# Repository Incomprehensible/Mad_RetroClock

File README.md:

# Retro style desk clock

Powered via 5V USB-C interface. Provides a 2S Li-Ion battery pack for autonomous operation.\
Made with 4 IN-12A Nixie Tubes denoting hours & minutes, and smaller INS-1 tubes as the dots.\
Enabled with Wi-Fi connectivity for automatic time synchronization using the Network Time Protocol (NTP).\
Functions as a simple clock and an alarm clock. User interface for the alarm setting is implemented with 2 Set/Unset buttons and rotary encoder.\
There's an MP3-player onboard any melody can be programmed and set as an alarm call.

## Gallery

<details><summary>More photos</summary>

</details>

## Further steps
* Enclosure design
* Add remote app control / IOT host node connectivity
* Better power design to get rid of inrush current issue preventing the device to start up sometimes without USB power attached

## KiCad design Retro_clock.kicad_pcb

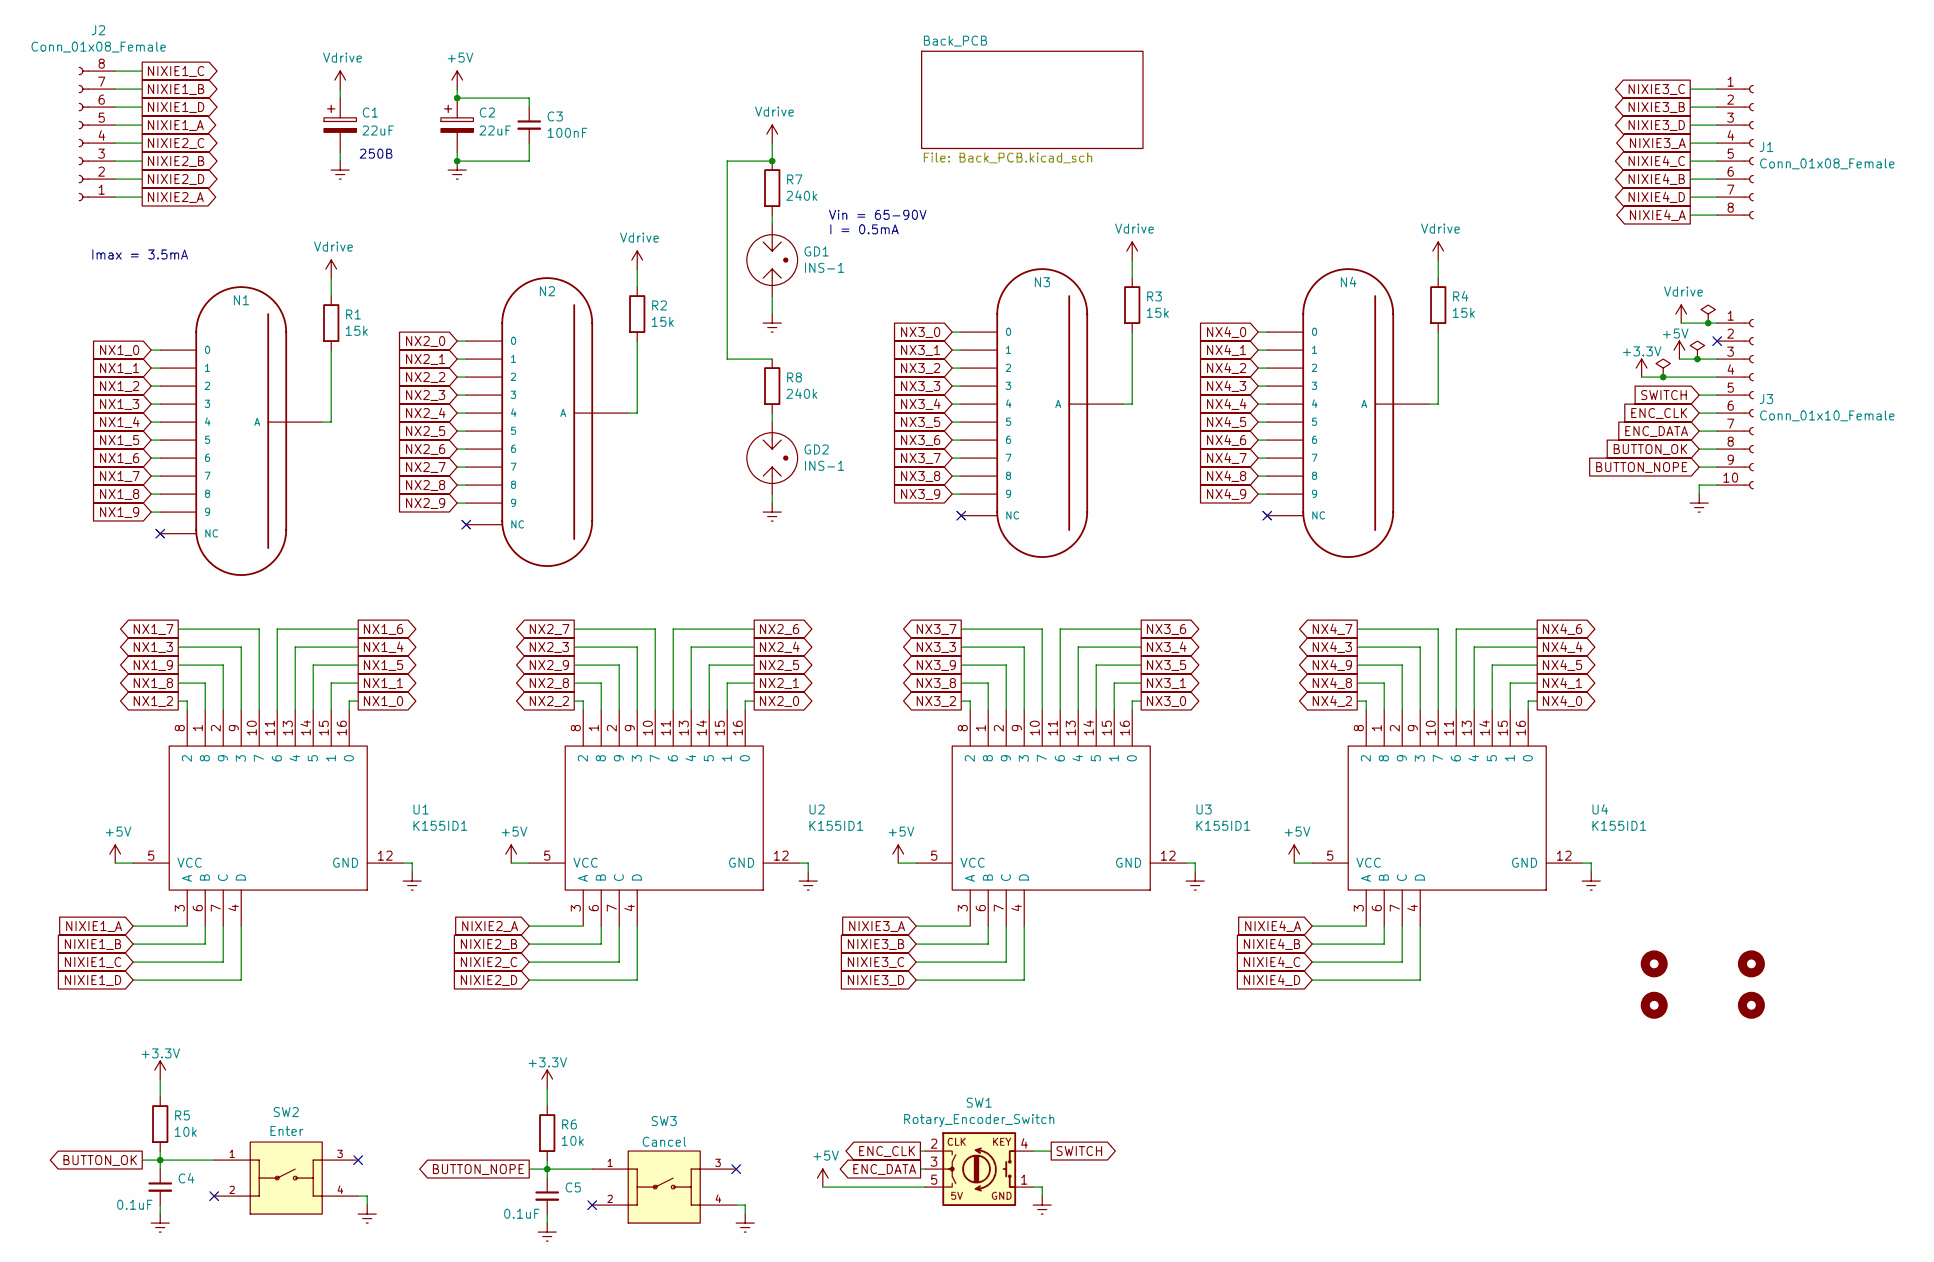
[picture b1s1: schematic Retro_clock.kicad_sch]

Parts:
C1: 22uF; CP_Radial_D10.0mm_P5.00mm
C2: 22uF; CP_EIA-3216-10_Kemet-I_Pad1.58x1.35mm_HandSolder
C3: 100nF; C_0603_1608Metric_Pad1.08x0.95mm_HandSolder
C4, C5: 0.1uF; C_0603_1608Metric_Pad1.08x0.95mm_HandSolder
GD1, GD2: INS-1
H1, H2, H3, H4: MountingHole; MountingHole_2.5mm_Pad_Via
J1, J2: Conn_01x08_Female; PinSocket_1x08_P2.54mm_Vertical
J3: Conn_01x10_Female; PinSocket_1x10_P2.54mm_Vertical
N1, N2, N3, N4: IN-12A
R1, R2, R3, R4: 15k; R_1206_3216Metric_Pad1.30x1.75mm_HandSolder
R5, R6: 10k; R_1206_3216Metric_Pad1.30x1.75mm_HandSolder
R7, R8: 240k; R_0805_2012Metric_Pad1.20x1.40mm_HandSolder
SW1: Rotary_Encoder_Switch; Encoder
SW2: Enter; KLS7-TS6601-13.0-180
SW3: Cancel; KLS7-TS6601-13.0-180
U1, U2, U3, U4: K155ID1; DIP-16_W7.62mm

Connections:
+3.3V: J3.4, R5.1, R6.1
+5V: C2.1, C3.1, J3.3, SW1.5 (5V), U1.5 (VCC), U2.5 (VCC), U3.5 (VCC), U4.5 (VCC)
BUTTON_NOPE: C5.1, J3.9, R6.2, SW3.1
BUTTON_OK: C4.1, J3.8, R5.2, SW2.1
ENC_CLK: J3.6, SW1.2 (CLK)
ENC_DATA: J3.7, SW1.3 (DATA)
Earth: C1.2, C2.2, C3.2, C4.2, C5.2, GD1.2, GD2.2, J3.10, SW1.1 (GND), SW2.4, SW3.4, U1.12 (GND), U2.12 (GND), U3.12 (GND), U4.12 (GND)
NIXIE1_A: J2.5, U1.3 (A)
NIXIE1_B: J2.7, U1.6 (B)
NIXIE1_C: J2.8, U1.7 (C)
NIXIE1_D: J2.6, U1.4 (D)
NIXIE2_A: J2.1, U2.3 (A)
NIXIE2_B: J2.3, U2.6 (B)
NIXIE2_C: J2.4, U2.7 (C)
NIXIE2_D: J2.2, U2.4 (D)
NIXIE3_A: J1.4, U3.3 (A)
NIXIE3_B: J1.2, U3.6 (B)
NIXIE3_C: J1.1, U3.7 (C)
NIXIE3_D: J1.3, U3.4 (D)
NIXIE4_A: J1.8, U4.3 (A)
NIXIE4_B: J1.6, U4.6 (B)
NIXIE4_C: J1.5, U4.7 (C)
NIXIE4_D: J1.7, U4.4 (D)
NX1_0: N1.2 (0), U1.16 (0)
NX1_1: N1.11 (1), U1.15 (1)
NX1_2: N1.10 (2), U1.8 (2)
NX1_3: N1.9 (3), U1.9 (3)
NX1_4: N1.8 (4), U1.13 (4)
NX1_5: N1.7 (5), U1.14 (5)
NX1_6: N1.6, U1.11 (6)
NX1_7: N1.5 (7), U1.10 (7)
NX1_8: N1.4 (8), U1.1 (8)
NX1_9: N1.3 (9), U1.2 (9)
NX2_0: N2.2 (0), U2.16 (0)
NX2_1: N2.11 (1), U2.15 (1)
NX2_2: N2.10 (2), U2.8 (2)
NX2_3: N2.9 (3), U2.9 (3)
NX2_4: N2.8 (4), U2.13 (4)
NX2_5: N2.7 (5), U2.14 (5)
NX2_6: N2.6, U2.11 (6)
NX2_7: N2.5 (7), U2.10 (7)
NX2_8: N2.4 (8), U2.1 (8)
NX2_9: N2.3 (9), U2.2 (9)
NX3_0: N3.2 (0), U3.16 (0)
NX3_1: N3.11 (1), U3.15 (1)
NX3_2: N3.10 (2), U3.8 (2)
NX3_3: N3.9 (3), U3.9 (3)
NX3_4: N3.8 (4), U3.13 (4)
NX3_5: N3.7 (5), U3.14 (5)
NX3_6: N3.6, U3.11 (6)
NX3_7: N3.5 (7), U3.10 (7)
NX3_8: N3.4 (8), U3.1 (8)
NX3_9: N3.3 (9), U3.2 (9)
NX4_0: N4.2 (0), U4.16 (0)
NX4_1: N4.11 (1), U4.15 (1)
NX4_2: N4.10 (2), U4.8 (2)
NX4_3: N4.9 (3), U4.9 (3)
NX4_4: N4.8 (4), U4.13 (4)
NX4_5: N4.7 (5), U4.14 (5)
NX4_6: N4.6, U4.11 (6)
NX4_7: N4.5 (7), U4.10 (7)
NX4_8: N4.4 (8), U4.1 (8)
NX4_9: N4.3 (9), U4.2 (9)
unnamed: GD1.1, R7.2
unnamed: GD2.1, R8.2
unnamed: N1.1 (A), R1.2
unnamed: N2.1 (A), R2.2
unnamed: N3.1 (A), R3.2
unnamed: N4.1 (A), R4.2
SWITCH: J3.5, SW1.4 (KEY)
Vdrive: C1.1, J3.1, R1.1, R2.1, R3.1, R4.1, R7.1, R8.1

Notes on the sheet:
Imax = 3.5mA
Vin = 65-90V I = 0.5mA
250В

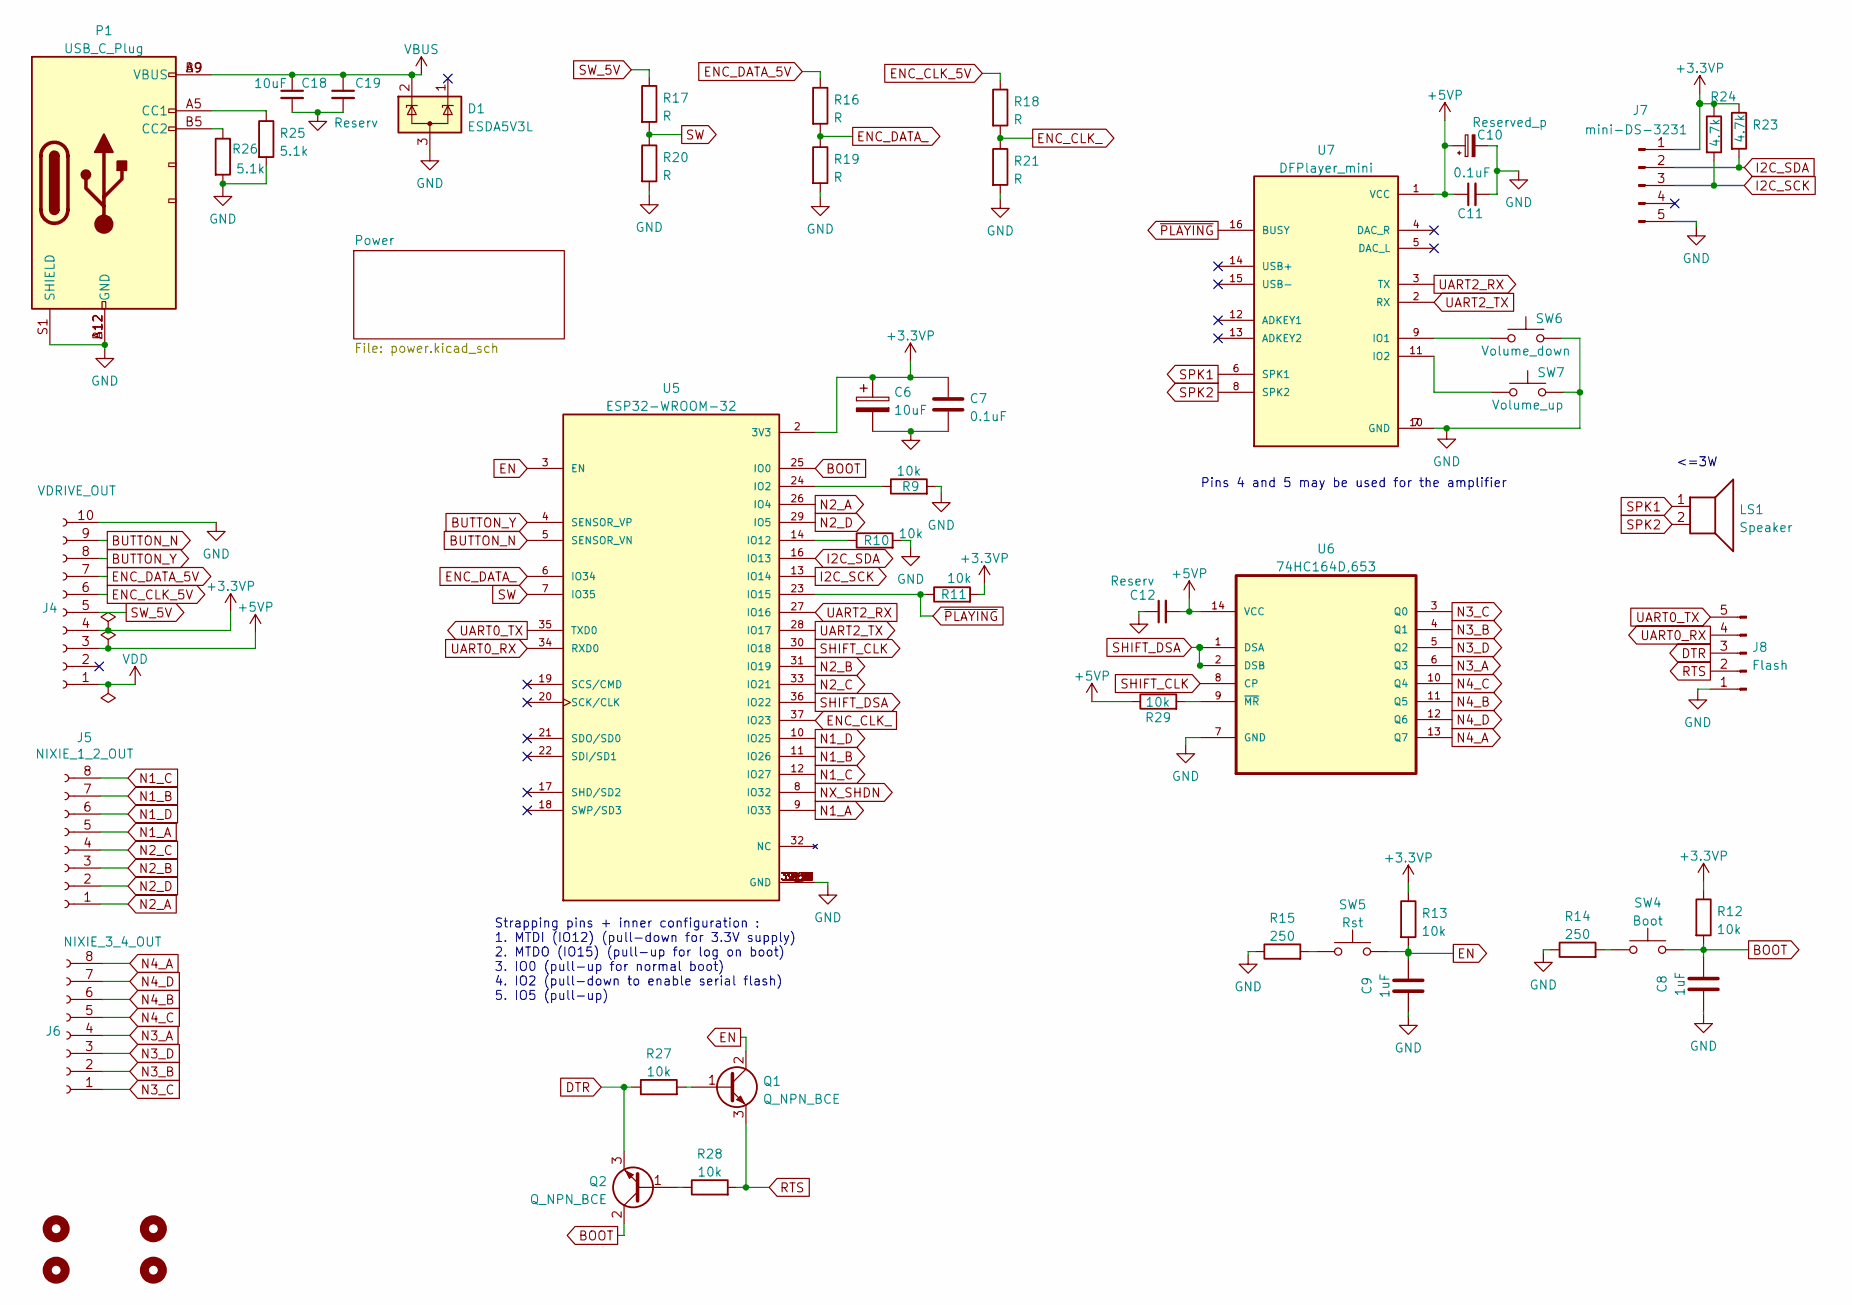
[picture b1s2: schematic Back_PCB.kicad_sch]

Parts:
C6, C18: 10uF; C_0603_1608Metric_Pad1.08x0.95mm_HandSolder
C7, C11: 0.1uF; C_0603_1608Metric_Pad1.08x0.95mm_HandSolder
C8, C9: 1uF; C_0603_1608Metric_Pad1.08x0.95mm_HandSolder
C10: Reserved_p; C_0603_1608Metric_Pad1.08x0.95mm_HandSolder
C12, C19: Reserv; C_0603_1608Metric_Pad1.08x0.95mm_HandSolder
D1: ESDA5V3L; SOT-23
H5, H6, H7, H8: MountingHole; MountingHole_2.5mm_Pad_Via
J4: VDRIVE_OUT; PinSocket_1x10_P2.54mm_Vertical
J5: NIXIE_1_2_OUT; PinSocket_1x08_P2.54mm_Vertical
J6: NIXIE_3_4_OUT; PinSocket_1x08_P2.54mm_Vertical
J7: mini-DS-3231; DS3231-Mini
J8: Flash; PinHeader_1x05_P2.54mm_Vertical
LS1: Speaker; Speaker_conn
P1: USB_C_Plug; usb_c_receptable_hro_type-c-31-m-17
Q1, Q2: Q_NPN_BCE; SOT-23_Handsoldering
R9, R10, R11, R12, R13, R27, R28, R29: 10k; R_0603_1608Metric_Pad0.98x0.95mm_HandSolder
R14, R15: 250; R_0603_1608Metric_Pad0.98x0.95mm_HandSolder
R16, R17, R18, R19, R20, R21: R; R_0603_1608Metric_Pad0.98x0.95mm_HandSolder
R23, R24: 4.7k; R_0603_1608Metric_Pad0.98x0.95mm_HandSolder
R25, R26: 5.1k; R_0603_1608Metric_Pad0.98x0.95mm_HandSolder
SW4: Boot; SW_TS-1187A-B-A-B
SW5: Rst; SW_TS-1187A-B-A-B
SW6: Volume_down; KLS7-TS6601-13.0-180
SW7: Volume_up; KLS7-TS6601-13.0-180
U5: ESP32-WROOM-32; MODULE_ESP32-WROOM-32; PARTREV 2.9
U6: 74HC164D,653; SOIC127P600X175-14N; MPN 74HC164D,653
U7: DFPlayer_mini; MODULE_DFR0299

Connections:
+3.3VP: C6.1, C7.1, J4.4, J7.1, R11.2, R12.1, R13.1, R23.1, R24.1, U5.2 (3V3); also elsewhere on the board
+5VP: C10.1, C11.1, C12.2, J4.3, R29.1, U6.14 (VCC), U7.1 (VCC); also elsewhere on the board
BOOT: C8.2, Q2.2 (C), R12.2, SW4.2, U5.25 (IO0)
BUTTON_N: J4.9, U5.5 (SENSOR_VN)
BUTTON_Y: J4.8, U5.4 (SENSOR_VP)
DTR: J8.3, Q2.3 (E), R27.1
EN: C9.2, Q1.2 (C), R13.2, SW5.2, U5.3 (EN)
ENC_CLK_: R18.2, R21.1, U5.37 (IO23)
ENC_CLK_5V: J4.6, R18.1
ENC_DATA_: R16.2, R19.1, U5.6 (IO34)
ENC_DATA_5V: J4.7, R16.1
GND: C6.2, C7.2, C8.1, C9.1, C10.2, C11.2, C12.1, C18.2, C19.2, D1.3 (A), J4.10, J7.5, J8.1, P1.A12 (GND), P1.B12 (GND), P1.S1 (SHIELD), R9.2, R10.2, R14.1, R15.1, R19.2, R20.2, R21.2, R25.2, R26.2, SW6.2, SW7.2, U5.1 (GND), U5.15 (GND), U5.38 (GND), U5.39_1 (GND), U5.39_2 (GND), U5.39_3 (GND), U5.39_4 (GND), U5.39_5 (GND), U5.39_6 (GND), U5.39_7 (GND), U5.39_8 (GND), U5.39_9 (GND), U5.39_10 (GND), U5.39_11 (GND), U5.39_12 (GND), U5.39_13 (GND), U5.39_14 (GND), U5.39_15 (GND), U5.39_16 (GND), U5.39_17 (GND), U5.39_18 (GND), U5.39_19 (GND), U5.39_20 (GND), U5.39_21 (GND), U6.7 (GND), U7.7 (GND), U7.10 (GND); also elsewhere on the board
I2C_SCK: J7.3, R24.2, U5.13 (IO14)
I2C_SDA: J7.2, R23.2, U5.16 (IO13)
N1_A: J5.5, U5.9 (IO33)
N1_B: J5.7, U5.11 (IO26)
N1_C: J5.8, U5.12 (IO27)
N1_D: J5.6, U5.10 (IO25)
N2_A: J5.1, U5.26 (IO4)
N2_B: J5.3, U5.31 (IO19)
N2_C: J5.4, U5.33 (IO21)
N2_D: J5.2, U5.29 (IO5)
N3_A: J6.4, U6.6 (Q3)
N3_B: J6.2, U6.4 (Q1)
N3_C: J6.1, U6.3 (Q0)
N3_D: J6.3, U6.5 (Q2)
N4_A: J6.8, U6.13 (Q7)
N4_B: J6.6, U6.11 (Q5)
N4_C: J6.5, U6.10 (Q4)
N4_D: J6.7, U6.12 (Q6)
NX_SHDN: U5.8 (IO32); also elsewhere on the board
unnamed: P1.A5 (CC1), R25.1
unnamed: P1.B5 (CC2), R26.1
unnamed: Q1.1 (B), R27.2
unnamed: Q2.1 (B), R28.1
unnamed: R9.1, U5.24 (IO2)
unnamed: R10.1, U5.14 (IO12)
unnamed: R14.2, SW4.1
unnamed: R15.2, SW5.1
unnamed: R29.2, U6.9 (~MR)
unnamed: SW6.1, U7.9 (IO1)
unnamed: SW7.1, U7.11 (IO2)
RTS: J8.2, Q1.3 (E), R28.2
SHIFT_CLK: U5.30 (IO18), U6.8 (CP)
SHIFT_DSA: U5.36 (IO22), U6.1 (DSA)
SPK1: LS1.1, U7.6 (SPK1)
SPK2: LS1.2, U7.8 (SPK2)
SW: R17.2, R20.1, U5.7 (IO35)
SW_5V: J4.5, R17.1
UART0_RX: J8.4, U5.34 (RXD0)
UART0_TX: J8.5, U5.35 (TXD0)
UART2_RX: U5.27 (IO16), U7.3 (TX)
UART2_TX: U5.28 (IO17), U7.2 (RX)
VBUS: C18.1, C19.1, D1.2 (K), P1.A9 (VBUS), P1.B9 (VBUS); also elsewhere on the board
VDD: J4.1; also elsewhere on the board
~PLAYING: R11.1, U5.23 (IO15), U7.16 (BUSY)

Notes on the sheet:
<=3W
Pins 4 and 5 may be used for the amplifier
Strapping pins + inner configuration : 1. MTDI (IO12) (pull-down for 3.3V supply) 2. MTDO (IO15) (pull-up for log on boot) 3. IO0 (pull-up for normal boot) 4. IO2 (pull-down to enable serial flash) 5. IO5 (pull-up)

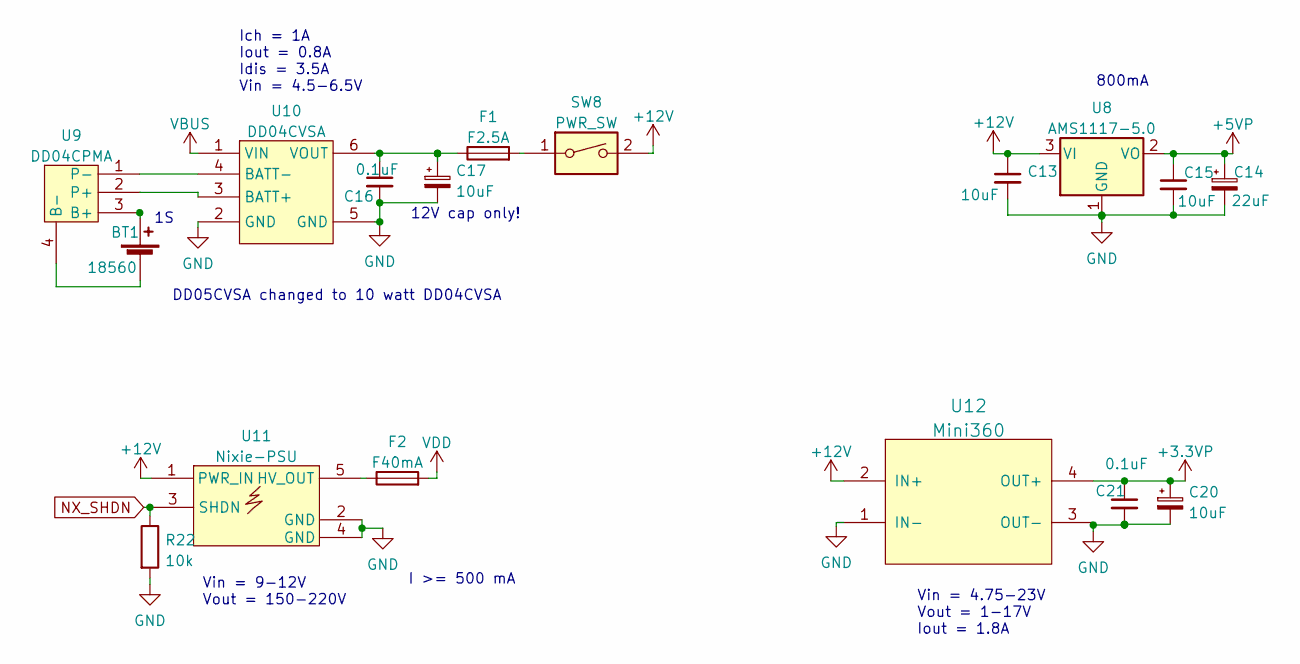
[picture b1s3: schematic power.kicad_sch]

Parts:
BT1: 18560; BAT_BH-18650-PC
C13, C15, C20: 10uF; C_0603_1608Metric_Pad1.08x0.95mm_HandSolder
C14: 22uF; CP_EIA-3216-10_Kemet-I_Pad1.58x1.35mm_HandSolder
C16, C21: 0.1uF; C_0603_1608Metric_Pad1.08x0.95mm_HandSolder
C17: 10uF; C_0805_2012Metric_Pad1.18x1.45mm_HandSolder
F1: F2.5A; Fuse_1206_3216Metric_Pad1.42x1.75mm_HandSolder
F2: F40mA; Fuse_1206_3216Metric_Pad1.42x1.75mm_HandSolder
R22: 10k; R_0603_1608Metric_Pad0.98x0.95mm_HandSolder
SW8: PWR_SW; PWR_SWITCH
U8: AMS1117-5.0; SOT-223-3_TabPin2
U9: DD04CPMA
U10: DD04CVSA
U11: Nixie-PSU
U12: Mini360; Mini360_step-down

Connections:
+3.3VP: C20.1, C21.1, U12.4 (OUT+); also elsewhere on the board
+5VP: C14.1, C15.1, U8.2 (VO); also elsewhere on the board
+12V: C13.1, SW8.2, U8.3 (VI), U11.1 (PWR_IN), U12.2 (IN+)
GND: C13.2, C14.2, C15.2, C16.2, C17.2, C20.2, C21.2, R22.2, U8.1 (GND), U10.2 (GND), U10.5 (GND), U11.2 (GND), U11.4 (GND), U12.1 (IN-), U12.3 (OUT-); also elsewhere on the board
NX_SHDN: R22.1, U11.3 (SHDN); also elsewhere on the board
unnamed: BT1.1 (+), U9.3 (B+)
unnamed: BT1.2 (-), U9.4 (B-)
unnamed: C16.1, C17.1, F1.1, U10.6 (VOUT)
unnamed: F1.2, SW8.1
unnamed: F2.1, U11.5 (HV_OUT)
unnamed: U9.2 (P+), U10.3 (BATT+)
unnamed: U9.1 (P-), U10.4 (BATT-)
VBUS: U10.1 (VIN); also elsewhere on the board
VDD: F2.2; also elsewhere on the board

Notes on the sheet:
Vin = 9-12V Vout = 150-220V
800mA
DD05CVSA changed to 10 watt DD04CVSA
12V cap only!
Vin = 4.75-23V Vout = 1-17V Iout = 1.8A
Ich = 1A Iout = 0.8A Idis = 3.5A Vin = 4.5-6.5V
I >= 500 mA

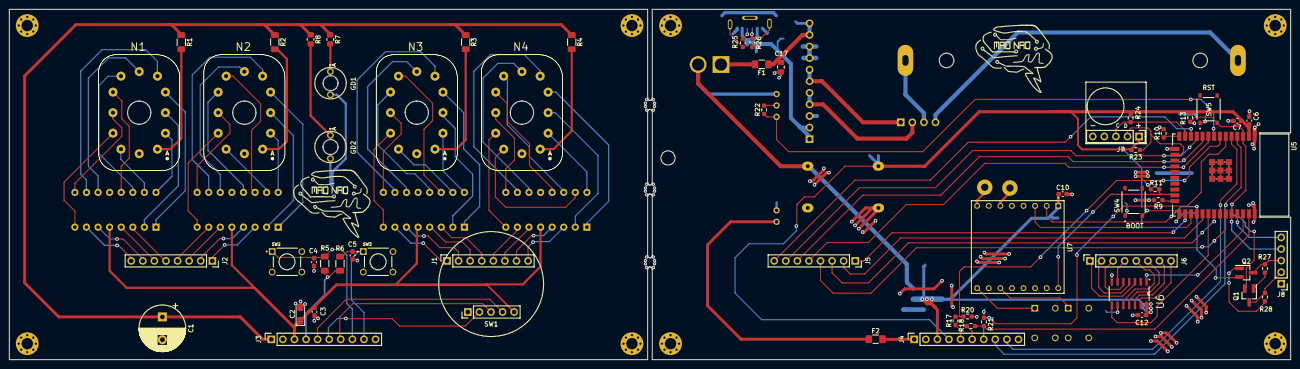
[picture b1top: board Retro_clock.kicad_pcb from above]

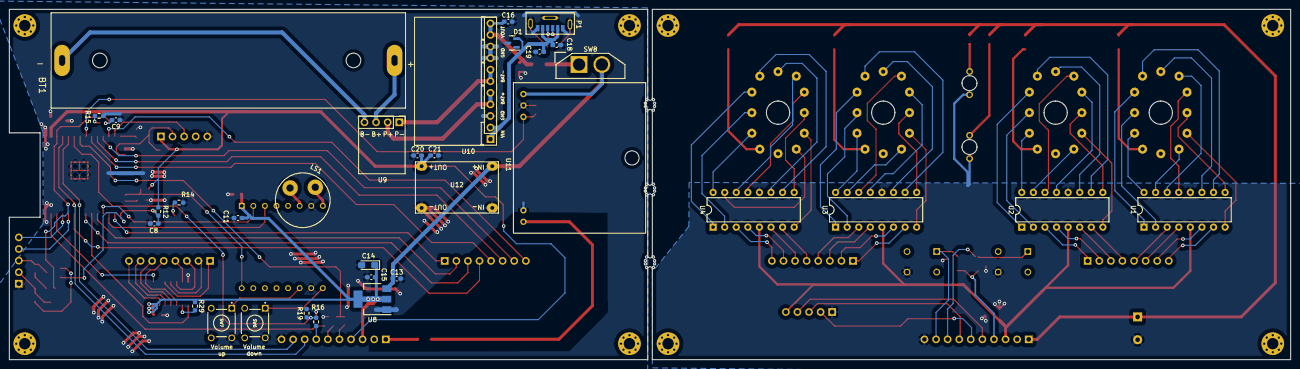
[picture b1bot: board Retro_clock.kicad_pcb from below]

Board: 2 copper layers, 280.9 x 76.8 mm, 103 parts (33 on the bottom side), 135 nets.

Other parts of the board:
mouse-bite-1mm-slot, mouse-bite-1mm-slot#2, mouse-bite-1mm-slot#3: VAL**; mouse-bite-1mm-slot

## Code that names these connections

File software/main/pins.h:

#ifndef PINS_H
#define PINS_H

#include "driver/gpio.h"

#define SHDN_PIN GPIO_NUM_32
#define BUTTON_Y_PIN GPIO_NUM_36 // SENSOR_VP
#define BUTTON_N_PIN GPIO_NUM_39 //SENSOR_VN
#define ENC_DATA_PIN GPIO_NUM_34
#define ENC_CLK_PIN GPIO_NUM_23
#define SWITCH_PIN GPIO_NUM_35
#define N1A_PIN GPIO_NUM_33
#define N1B_PIN GPIO_NUM_26
#define N1C_PIN GPIO_NUM_27
#define N1D_PIN GPIO_NUM_25
#define N2A_PIN GPIO_NUM_4
#define N2B_PIN GPIO_NUM_19
#define N2C_PIN GPIO_NUM_21
#define N2D_PIN GPIO_NUM_5
#define SHIFT_CLK_PIN GPIO_NUM_18
#define SHIFT_DSA_PIN GPIO_NUM_22
#define PLAYING_PIN GPIO_NUM_15
#define I2C_SDA_PIN GPIO_NUM_13
#define I2C_SCL_PIN GPIO_NUM_14
#define UART_TX_PIN GPIO_NUM_17
#define UART_RX_PIN GPIO_NUM_16

#endif

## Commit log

2022-07-14 First PCB ready.
2022-07-22 Finished first pcb, 2nd schematics and footprints.
2022-07-24 Final version without panelization.
2022-07-25 Fixed some minor things, added panelization.
2022-07-25 Update README.
2022-09-05 Added code for shift register, i2c check.
2022-09-07 Added Wifi NTP client, RTC code, time visualization.
2022-09-14 Added code for RTC, encoder, small logic for alarm.
2022-10-23 Changed locale, added code for DFPlayer. Notice: MH2024K responds correctly only after SD card is inserted.
2022-10-29 Added debug funcs, fixed first number range, added player sleep mode.
2024-09-16 Added picture gallery.
2024-09-16 Create LICENSE
